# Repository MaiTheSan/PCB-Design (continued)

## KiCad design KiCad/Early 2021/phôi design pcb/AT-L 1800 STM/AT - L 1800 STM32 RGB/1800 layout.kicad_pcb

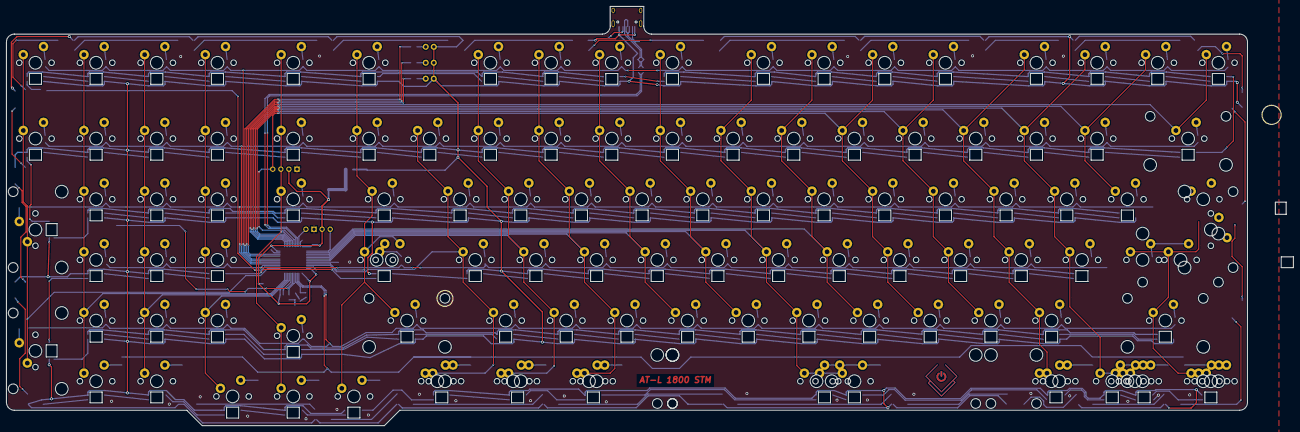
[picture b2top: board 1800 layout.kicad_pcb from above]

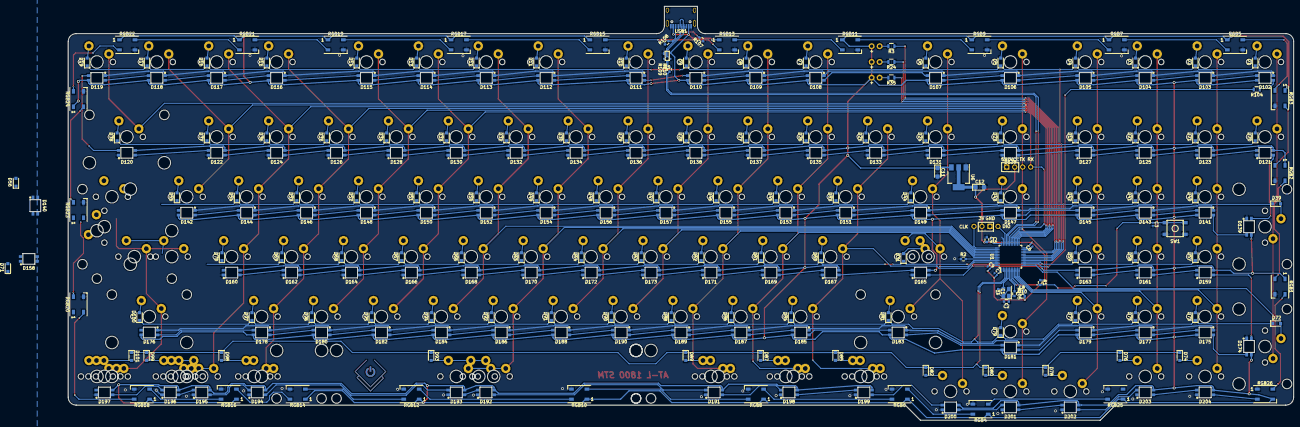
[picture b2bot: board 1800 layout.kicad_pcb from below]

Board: 2 copper layers, 404.1 x 131.6 mm, 380 parts (259 on the bottom side), 278 nets.

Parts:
C1, C2: 22pF; C_0603
C3, C5, C6, C7, C9: 0.1uF; C_0402_1005Metric
C4: 10uF; C_0603
C8: 10nF; C_0402_1005Metric
C10: 1uF; C_0603
C11, C12: >=22uF; CP_EIA-3216-12_Kemet-S
D1, D2, D3, D4, D5, D6, D7, D8, D9, D10, D11, D12, D13, D14, D15, D16, D17, D19, D20, D21, D22, D23, D24, D25, D26, D27, D28, D29, D30, D32, D33, D34, D35, D36, D37, D38, D39, D40, D41, D42, D43, D44, D45, D46, D47, D48, D49, D50, D51, D52, D53, D54, D55, D56, D57, D58, D59, D60, D61, D62, D63, D64, D65, D66, D67, D68, D69, D70, D71, D72, D73, D74, D75, D76, D77, D78, D79, D80, D81, D82, D83, D84, D85, D86, D87, D88, D89, D90, D91, D92, D93, D94, D95, D96, D97, D98, D99, D100, D101: D; D_SOD-323_HandSoldering
D18, D31: SOD123; D_SOD-323_HandSoldering
D102, D103, D104, D105, D106, D107, D108, D109, D110, D111, D112, D113, D114, D115, D116, D117, D118, D119, D140, D141, D142, D143, D144, D145, D146, D147, D148, D149, D150, D151, D152, D153, D154, D155, D156, D157, D175, D176, D177, D178, D179, D180, D181, D182, D183, D184, D185, D186, D187, D188, D189, D190: SK6812; RGB-6028_FLIPPED
D120, D121, D122, D123, D124, D125, D126, D127, D128, D129, D130, D131, D132, D133, D134, D135, D136, D137, D138, D139, D158, D159, D160, D161, D162, D163, D164, D165, D166, D167, D168, D169, D170, D171, D172, D173, D174, D191, D192, D193, D194, D195, D196, D197, D198, D199, D200, D201, D202, D203, D204: SK6812; RGB-6028
LOGO1: Logo_Open_Hardware_Large; sanpjxlogo
Led1, Led2, Led3: LED; MXOnly-LEDONLY-MID
MX_1, MX_2, MX_3, MX_4, MX_5, MX_6, MX_7, MX_8, MX_9, MX_10: 1U; MXOnly-1U-NoLED
MX_'1: 1U; MXOnly-1U-NoLED
MX_+1: 1U; MXOnly-1U-NoLED
MX_-1: 1U; MXOnly-1U-NoLED
MX_/?/1: 1U; MXOnly-1U-NoLED
MX_;1: 1U; MXOnly-1U-NoLED
MX_<1: 1U; MXOnly-1U-NoLED
MX_>1: 1U; MXOnly-1U-NoLED
MX_A1: 1U; MXOnly-1U-NoLED
MX_ALT1: 1,5U; MXOnly-1.5U-NoLED
MX_ALT2: 1,25U FLIPPED; MXOnly-1.25U-NoLED
MX_BkSp1: 2U FLIPPED; MXOnly-2U-NoLED
MX_CapLk1: 1,75U; MXOnly-1.75U-NoLED
MX_CapLk2: 1,25U FLIPPED; MXOnly-1.25U-NoLED
MX_D1: 1U; MXOnly-1U-NoLED
MX_Delete1: 1U; MXOnly-1U-NoLED
MX_Down1: 1U; MXOnly-1U-NoLED
MX_E1: 1U; MXOnly-1U-NoLED
MX_ENTER1: 2x2.25U ISO enter; MXOnly-ISO-ROTATED-ReversedStabilizers-NoLED
MX_ENTER2: 2,25U FLIPPED; MXOnly-2.25U-ReversedStabilizers-NoLED
MX_ESC1: 1U FLIPPED; MXOnly-1U-NoLED
MX_F1, MX_F4, MX_F5, MX_F6, MX_F8, MX_F10, MX_F11: 1U; MXOnly-1U-NoLED
MX_F2, MX_F3, MX_F7, MX_F9, MX_F12, MX_F13: 1U FLIPPED; MXOnly-1U-NoLED
MX_FN1, MX_FN2, MX_FN3, MX_FN41: 1U; MXOnly-1U-NoLED
MX_FN4: 1U_FLIPPED; MXOnly-1U-NoLED
MX_G1: 1U; MXOnly-1U-NoLED
MX_H1: 1U; MXOnly-1U-NoLED
MX_I1: 1U; MXOnly-1U-NoLED
MX_J1: 1U; MXOnly-1U-NoLED
MX_K1: 1U; MXOnly-1U-NoLED
MX_L1: 1U; MXOnly-1U-NoLED
MX_LControl1: 1,5U; MXOnly-1.5U-NoLED
MX_LControl2: 1,25U FLIPPED; MXOnly-1.25U-NoLED
MX_LShift1: 2,25U; MXOnly-2.25U-NoLED
MX_LWin1: 1U; MXOnly-1U-NoLED
MX_LWin2: 1,25U NoLed; MXOnly-1.25U-NoLED
MX_Left1: 1U; MXOnly-1U-NoLED
MX_O1: 1U; MXOnly-1U-NoLED
MX_P1: 1U; MXOnly-1U-NoLED
MX_Q1: 1U; MXOnly-1U-NoLED
MX_R1: 1U; MXOnly-1U-NoLED
MX_RAlt1: 1,25U; MXOnly-1.25U-NoLED
MX_RAlt2: 1,5U FLIPPED; MXOnly-1.5U-NoLED
MX_RAlt3: 1,5U; MXOnly-1.5U-NoLED
MX_RControl1: 1,25U NoLed; MXOnly-1.25U-NoLED
MX_RControl2: 1U FLIPPED; MXOnly-1U-NoLED
MX_RControl3: 1,5U FLIPPED; MXOnly-1.5U-NoLED
MX_RShift1: 2,75U FLIPPED; MXOnly-2.75U-NoLED
MX_RWin1: NoLed; MXOnly-1.25U-NoLED
MX_RWin2: 1,5U; MXOnly-1.5U-NoLED
MX_RWin3: 1U; MXOnly-1U-NoLED
MX_S1: 1U; MXOnly-1U-NoLED
MX_SpaceBar1, MX_SpaceBar2: 6,25U FLIPPED; MXOnly-6.25U-ReversedStabilizers-NoLED
MX_SpaceBar3: 7U; MXOnly-7U-ReversedStabilizers-NoLED
MX_T1: 1U; MXOnly-1U-NoLED
MX_U1: 1U; MXOnly-1U-NoLED
MX_W1: 1U; MXOnly-1U-NoLED
MX_Y1: 1U; MXOnly-1U-NoLED
MX_[1: 1U; MXOnly-1U-NoLED
MX_]1: 1U; MXOnly-1U-NoLED
MX_`~1: 1U; MXOnly-1U-NoLED
MX_b1: 1U; MXOnly-1U-NoLED
MX_c1: 1U; MXOnly-1U-NoLED
MX_insert1: 1U; MXOnly-1U-NoLED
MX_m1: 1U; MXOnly-1U-NoLED
MX_n1: 1U; MXOnly-1U-NoLED
MX_num1, MX_num2, MX_num3, MX_num4, MX_num5, MX_num6, MX_num7, MX_num8, MX_num9, MX_num10: 1U; MXOnly-1U-NoLED
MX_num*1: 1U; MXOnly-1U-NoLED
MX_num+1: 2U FLIPPED; MXOnly-2U-NoLED
MX_num-1: 1U; MXOnly-1U-NoLED
MX_num/1: 1U; MXOnly-1U-NoLED
MX_numDel1: 1U; MXOnly-1U-NoLED
MX_numEnter1: 2U; MXOnly-2U-NoLED
MX_numLk1: 1U; MXOnly-1U-NoLED
MX_right1: 1U; MXOnly-1U-NoLED
MX_tab1: 1,5U; MXOnly-1.5U-NoLED
MX_up1: 1U; MXOnly-1U-NoLED
MX_v1: 1U; MXOnly-1U-NoLED
MX_x1: 1U; MXOnly-1U-NoLED
MX_z1: 1U; MXOnly-1U-NoLED
MX_|\1: 1U; MXOnly-1U-NoLED
MX_|\2: 1.5U FLIPPED; MXOnly-1.5U-NoLED
R1, R2: 10k; C_0603
R3, R24, R35: 300; R_0805
R104: 500; R_0805
R105: 390; C_0603
R107, R108: 5.1k; C_0603
R109, R110: 22; C_0603
RGB1, RGB2, RGB3, RGB4, RGB5, RGB6, RGB7, RGB8, RGB9, RGB10, RGB11, RGB12, RGB13, RGB14, RGB15, RGB16, RGB17, RGB18, RGB19, RGB20, RGB21, RGB22, RGB23, RGB24, RGB25, RGB26: WS2812B; LED_WS2812B_PLCC4_5.0x5.0mm_P3.2mm
SW1: SW_Push; SKQG-1155865
U1: STM32F303CCTx; LQFP-48_7x7mm_P0.5mm
U2, U3: OLED-Pin; 0.91_SSD1306_OLED
U5: PRTR5V0U2X; SOT143B
U6: AMS1117-3.3; SOT-223-3_TabPin2
USB1: HRO-TYPE-C-31-M-12; HRO-TYPE-C-31-M-12-Assembly
Y1: 16Mhz; Crystal_SMD_3225-4Pin_3.2x2.5mm

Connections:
+5V: C11.1, D102.1, D103.1, D104.1, D105.1, D106.1, D107.1, D108.1, D109.1, D110.1, D111.1, D112.1, D113.1, D114.1, D115.1, D116.1, D117.1, D118.1, D119.1, D120.1, D121.1, D122.1, D123.1, D124.1, D125.1, D126.1, D127.1, D128.1, D129.1, D130.1, D131.1, D132.1, D133.1, D134.1, D135.1, D136.1, D137.1, D138.1, D139.1, D140.1, D141.1, D142.1, D143.1, D144.1, D145.1, D146.1, D147.1, D148.1, D149.1, D150.1, D151.1, D152.1, D153.1, D154.1, D155.1, D156.1, D157.1, D158.1, D159.1, D160.1, D161.1, D162.1, D163.1, D164.1, D165.1, D166.1, D167.1, D168.1, D169.1, D170.1, D171.1, D172.1, D173.1, D174.1, D175.1, D176.1, D177.1, D178.1, D179.1, D180.1, D181.1, D182.1, D183.1, D184.1, D185.1, D186.1, D187.1, D188.1, D189.1, D190.1, D191.1, D192.1, D193.1, D194.1, D195.1, D196.1, D197.1, D198.1, D199.1, D200.1, D201.1, D202.1, D203.1, D204.1, Led1.2, Led2.2, Led3.2, RGB1.1, RGB2.1, RGB3.1, RGB4.1, RGB5.1, RGB6.1, RGB7.1, RGB8.1, RGB9.1, RGB10.1, RGB11.1, RGB12.1, RGB13.1, RGB14.1, RGB15.1, RGB16.1, RGB17.1, RGB18.1, RGB19.1, RGB20.1, RGB21.1, RGB22.1, RGB23.1, RGB24.1, RGB25.1, RGB26.3, U5.4, U6.3, USB1.2, USB1.11
/R+: R110.2, U5.3, USB1.5, USB1.7
/R-: R109.2, U5.2, USB1.6, USB1.8
CapsLed: R3.1, U1.19
Col0: MX_FN1.1, MX_num+1.1, MX_num-1.1, MX_numEnter1.1, U1.13
Col1: MX_FN2.1, MX_num1.1, MX_num2.1, MX_num3.1, MX_num4.1, MX_num*1.1, U1.12
Col2: MX_FN3.1, MX_num5.1, MX_num6.1, MX_num7.1, MX_num/1.1, MX_numDel1.1, U1.11
Col3: MX_FN4.1, MX_Left1.1, MX_num8.1, MX_num9.1, MX_num10.1, MX_numLk1.1, U1.10
Col4: MX_Delete1.1, MX_Down1.1, MX_FN41.1, MX_insert1.1, MX_up1.1, U1.30, U3.3
Col5: MX_CapLk1.2, MX_CapLk2.1, MX_ESC1.1, MX_LShift1.1, MX_`~1.1, MX_right1.1, MX_tab1.1, U1.45
Col6: MX_1.1, MX_A1.1, MX_LControl1.1, MX_LControl2.1, MX_Q1.1, MX_z1.1, U1.46
Col7: MX_2.1, MX_F1.1, MX_LWin1.1, MX_LWin2.1, MX_S1.1, MX_W1.1, MX_x1.1, U1.43
Col8: MX_3.1, MX_ALT1.1, MX_ALT2.1, MX_D1.1, MX_E1.1, MX_F2.1, MX_c1.1, U1.42
Col9: MX_4.1, MX_F3.1, MX_F4.1, MX_R1.1, MX_v1.1, U1.41
Col10: MX_5.1, MX_F5.1, MX_G1.1, MX_T1.1, MX_b1.1, U1.40
Col11: MX_6.1, MX_F6.1, MX_H1.1, MX_SpaceBar1.1, MX_SpaceBar2.1, MX_SpaceBar3.1, MX_Y1.1, MX_n1.1, U1.39
Col12: MX_7.1, MX_F7.1, MX_J1.1, MX_U1.1, MX_m1.1, U1.38
Col13: MX_8.1, MX_<1.1, MX_F8.1, MX_I1.1, MX_K1.1, U1.31, U3.4
Col14: MX_9.1, MX_>1.1, MX_F9.1, MX_L1.1, MX_O1.1, U1.29
Col15: MX_10.1, MX_/?/1.1, MX_;1.1, MX_F10.1, MX_P1.1, MX_RAlt1.1, MX_RAlt2.1, U1.28
Col16: MX_'1.1, MX_-1.1, MX_F11.1, MX_RAlt3.1, MX_RWin1.1, MX_RWin2.1, MX_RWin3.1, MX_[1.1, U1.27
Col17: MX_+1.1, MX_F12.1, MX_]1.1, U1.26
Col18: MX_BkSp1.1, MX_ENTER1.1, MX_ENTER2.1, MX_F13.1, MX_RControl1.1, MX_RControl2.1, MX_RControl3.1, MX_RShift1.1, MX_|\1.1, MX_|\2.1, U1.25
D+: R109.1, U1.33
D-: R110.1, U1.32
GND: C1.2, C2.2, C3.2, C4.1, C5.1, C6.1, C7.1, C8.1, C9.1, C10.1, C11.2, C12.2, D102.3, D103.3, D104.3, D105.3, D106.3, D107.3, D108.3, D109.3, D110.3, D111.3, D112.3, D113.3, D114.3, D115.3, D116.3, D117.3, D118.3, D119.3, D120.3, D121.3, D122.3, D123.3, D124.3, D125.3, D126.3, D127.3, D128.3, D129.3, D130.3, D131.3, D132.3, D133.3, D134.3, D135.3, D136.3, D137.3, D138.3, D139.3, D140.3, D141.3, D142.3, D143.3, D144.3, D145.3, D146.3, D147.3, D148.3, D149.3, D150.3, D151.3, D152.3, D153.3, D154.3, D155.3, D156.3, D157.3, D158.3, D159.3, D160.3, D161.3, D162.3, D163.3, D164.3, D165.3, D166.3, D167.3, D168.3, D169.3, D170.3, D171.3, D172.3, D173.3, D174.3, D175.3, D176.3, D177.3, D178.3, D179.3, D180.3, D181.3, D182.3, D183.3, D184.3, D185.3, D186.3, D187.3, D188.3, D189.3, D190.3, D191.3, D192.3, D193.3, D194.3, D195.3, D196.3, D197.3, D198.3, D199.3, D200.3, D201.3, D202.3, D203.3, D204.3, R2.1, R107.1, R108.1, RGB1.3, RGB2.3, RGB3.3, RGB4.3, RGB5.3, RGB6.3, RGB7.3, RGB8.3, RGB9.3, RGB10.3, RGB11.3, RGB12.3, RGB13.3, RGB14.3, RGB15.3, RGB16.3, RGB17.3, RGB18.3, RGB19.3, RGB20.3, RGB21.3, RGB22.3, RGB23.3, RGB24.3, RGB25.3, RGB26.1, SW1.1, U1.8, U1.23, U1.35, U1.47, U2.1, U3.1, U5.1, U6.1, USB1.1, USB1.12, USB1.13, Y1.2, Y1.4
LedRGB: D102.4, R104.1
LedRGBStrip: D204.2, RGB26.2
unnamed: C1.1, U1.5, Y1.3
unnamed: C2.1, R105.2, Y1.1
unnamed: C3.1, R1.2, SW1.2, U1.7
unnamed: D1.2, MX_FN1.2
unnamed: D2.2, MX_FN2.2
unnamed: D3.2, MX_FN3.2
unnamed: D4.2, MX_FN4.2
unnamed: D5.2, MX_FN41.2
unnamed: D6.2, MX_ESC1.2
unnamed: D7.2, MX_F1.2
unnamed: D8.2, MX_F2.2
unnamed: D9.2, MX_F3.2
unnamed: D10.2, MX_F5.2
unnamed: D11.2, MX_F6.2
unnamed: D12.2, MX_F7.2
unnamed: D13.2, MX_F8.2
unnamed: D14.2, MX_F9.2
unnamed: D15.2, MX_F10.2
unnamed: D16.2, MX_F11.2
unnamed: D17.2, MX_F12.2
unnamed: D18.2, MX_numLk1.2
unnamed: D19.2, MX_F13.2
unnamed: D20.2, MX_num-1.2
unnamed: D21.2, MX_num*1.2
unnamed: D22.2, MX_num/1.2
unnamed: D23.2, MX_insert1.2
unnamed: D24.2, MX_`~1.2
unnamed: D25.2, MX_1.2
unnamed: D26.2, MX_2.2
unnamed: D27.2, MX_3.2
unnamed: D28.2, MX_4.2
unnamed: D29.2, MX_5.2
unnamed: D30.2, MX_6.2
unnamed: D31.2, MX_CapLk1.1, MX_CapLk2.2
unnamed: D32.2, MX_7.2
unnamed: D33.2, MX_8.2
unnamed: D34.2, MX_9.2
unnamed: D35.2, MX_10.2
unnamed: D36.2, MX_-1.2
unnamed: D37.2, MX_+1.2
unnamed: D38.2, MX_BkSp1.2
unnamed: D39.2, MX_num+1.2
unnamed: D40.2, MX_num1.2
unnamed: D41.2, MX_num5.2
unnamed: D42.2, MX_num8.2
unnamed: D43.2, MX_Delete1.2
unnamed: D44.2, MX_tab1.2
unnamed: D45.2, MX_W1.2
unnamed: D46.2, MX_E1.2
unnamed: D47.2, MX_R1.2
unnamed: D48.2, MX_T1.2
unnamed: D49.2, MX_Y1.2
unnamed: D50.2, MX_U1.2
unnamed: D51.2, MX_I1.2
unnamed: D52.2, MX_O1.2
unnamed: D53.2, MX_P1.2
unnamed: D54.2, MX_[1.2
unnamed: D55.2, MX_]1.2
unnamed: D56.2, MX_|\1.2, MX_|\2.2
unnamed: D57.2, MX_num2.2
unnamed: D58.2, MX_num6.2
unnamed: D59.2, MX_num9.2
unnamed: D60.2, MX_A1.2
unnamed: D61.2, MX_S1.2
unnamed: D62.2, MX_D1.2
unnamed: D63.2, MX_F4.2
unnamed: D64.2, MX_G1.2
unnamed: D65.2, MX_H1.2
unnamed: D66.2, MX_J1.2
unnamed: D67.2, MX_K1.2
unnamed: D68.2, MX_L1.2
unnamed: D69.2, MX_;1.2
unnamed: D70.2, MX_'1.2
unnamed: D71.2, MX_ENTER1.2, MX_ENTER2.2
unnamed: D72.2, MX_numEnter1.2
unnamed: D73.2, MX_num3.2
unnamed: D74.2, MX_num4.2
unnamed: D75.2, MX_num7.2
unnamed: D76.2, MX_numDel1.2
unnamed: D77.2, MX_num10.2
unnamed: D78.2, MX_Left1.2
unnamed: D79.2, MX_up1.2
unnamed: D80.2, MX_Down1.2
unnamed: D81.2, MX_LShift1.2
unnamed: D82.2, MX_right1.2
unnamed: D83.2, MX_Q1.2
unnamed: D84.2, MX_z1.2
unnamed: D85.2, MX_LControl1.2, MX_LControl2.2
unnamed: D86.2, MX_x1.2
unnamed: D87.2, MX_LWin1.2, MX_LWin2.2
unnamed: D88.2, MX_c1.2
unnamed: D89.2, MX_ALT1.2, MX_ALT2.2
unnamed: D90.2, MX_v1.2
unnamed: D91.2, MX_b1.2
unnamed: D92.2, MX_n1.2
unnamed: D93.2, MX_SpaceBar1.2, MX_SpaceBar2.2, MX_SpaceBar3.2
unnamed: D94.2, MX_m1.2
unnamed: D95.2, MX_<1.2
unnamed: D96.2, MX_>1.2
unnamed: D97.2, MX_/?/1.2
unnamed: D98.2, MX_RAlt1.2, MX_RAlt2.2
unnamed: D99.2, MX_RAlt3.2, MX_RWin1.2, MX_RWin2.2, MX_RWin3.2
unnamed: D100.2, MX_RShift1.2
unnamed: D101.2, MX_RControl1.2, MX_RControl2.2, MX_RControl3.2
unnamed: D102.2, D103.4
unnamed: D103.2, D104.4
unnamed: D104.2, D105.4
unnamed: D105.2, D106.4
unnamed: D106.2, D107.4
unnamed: D107.2, D108.4
unnamed: D108.2, D109.4
unnamed: D109.2, D110.4
unnamed: D110.2, D111.4
unnamed: D111.2, D112.4
unnamed: D112.2, D113.4
unnamed: D113.2, D114.4
unnamed: D114.2, D115.4
unnamed: D115.2, D116.4
unnamed: D116.2, D117.4
unnamed: D117.2, D118.4
unnamed: D118.2, D119.4
unnamed: D120.2, D122.4
unnamed: D121.4, D123.2
unnamed: D122.2, D124.4
unnamed: D123.4, D125.2
unnamed: D124.2, D126.4
unnamed: D125.4, D127.2
unnamed: D126.2, D128.4
unnamed: D127.4, D129.2
unnamed: D128.2, D130.4
unnamed: D129.4, D131.2
unnamed: D130.2, D132.4
unnamed: D131.4, D133.2
unnamed: D132.2, D134.4
unnamed: D133.4, D135.2
unnamed: D134.2, D136.4
unnamed: D135.4, D137.2
unnamed: D136.2, D138.4
unnamed: D137.4, D138.2
unnamed: D139.2, D141.4
unnamed: D140.4, D142.2
unnamed: D141.2, D143.4
unnamed: D142.4, D144.2
unnamed: D143.2, D145.4
unnamed: D144.4, D146.2
unnamed: D145.2, D147.4
unnamed: D146.4, D148.2
unnamed: D147.2, D149.4
unnamed: D148.4, D150.2
unnamed: D149.2, D151.4
unnamed: D150.4, D152.2
unnamed: D151.2, D153.4
unnamed: D152.4, D154.2
unnamed: D153.2, D155.4
unnamed: D154.4, D156.2
unnamed: D155.2, D157.4
unnamed: D156.4, D157.2
unnamed: D158.2, D160.4
unnamed: D159.2, D174.4
unnamed: D159.4, D161.2
unnamed: D160.2, D162.4
unnamed: D161.4, D163.2
unnamed: D162.2, D164.4
unnamed: D163.4, D165.2
unnamed: D164.2, D166.4
unnamed: D165.4, D167.2
unnamed: D166.2, D168.4
unnamed: D167.4, D169.2
unnamed: D168.2, D170.4
unnamed: D169.4, D171.2
unnamed: D170.2, D172.4
unnamed: D171.4, D173.2
unnamed: D172.2, D173.4
unnamed: D175.2, D177.4
unnamed: D176.4, D178.2
unnamed: D177.2, D179.4
unnamed: D178.4, D180.2
unnamed: D179.2, D181.4
unnamed: D180.4, D182.2
unnamed: D181.2, D183.4
unnamed: D182.4, D184.2
unnamed: D183.2, D185.4
unnamed: D184.4, D186.2
unnamed: D185.2, D187.4
unnamed: D186.4, D188.2
unnamed: D187.2, D189.4
unnamed: D188.4, D190.2
unnamed: D189.2, D190.4
unnamed: D191.2, D198.4
unnamed: D191.4, D192.2
unnamed: D192.4, D193.2
unnamed: D193.4, D194.2
unnamed: D194.4, D195.2
unnamed: D195.4, D196.2
unnamed: D196.4, D197.2
unnamed: D198.2, D199.4
unnamed: D199.2, D200.4
unnamed: D200.2, D201.4
unnamed: D201.2, D202.4
unnamed: D202.2, D203.4
unnamed: D203.2, D204.4
unnamed: Led1.1, R3.2
unnamed: Led2.1, R24.2
unnamed: Led3.1, R35.2
unnamed: R2.2, U1.44
unnamed: R104.2, U1.14
unnamed: R105.1, U1.6
unnamed: R107.2, USB1.4
unnamed: R108.2, USB1.10
unnamed: RGB1.2, RGB2.4
unnamed: RGB1.4, RGB26.4
unnamed: RGB2.2, RGB3.4
unnamed: RGB3.2, RGB5.4
unnamed: RGB4.4, RGB6.2
unnamed: RGB5.2, RGB7.4
unnamed: RGB6.4, RGB8.2
unnamed: RGB7.2, RGB9.4
unnamed: RGB8.4, RGB10.2
unnamed: RGB10.4, RGB12.2
unnamed: RGB11.2, RGB13.4
unnamed: RGB9.2, RGB11.4
unnamed: RGB12.4, RGB14.2
unnamed: RGB13.2, RGB15.4
unnamed: RGB14.4, RGB16.2
unnamed: RGB15.2, RGB17.4
unnamed: RGB16.4, RGB18.2
unnamed: RGB17.2, RGB19.4
unnamed: RGB18.4, RGB20.2
unnamed: RGB19.2, RGB21.4
unnamed: RGB20.4, RGB23.2
unnamed: RGB21.2, RGB22.4
unnamed: RGB22.2, RGB24.4
unnamed: RGB23.4, RGB24.2
unnamed: RGB4.2, RGB25.4
NumLed: R35.1, U1.22
Row0: D1.1, D2.1, D3.1, D4.1, D5.1, D6.1, D7.1, D8.1, D9.1, D10.1, D11.1, D12.1, D13.1, D14.1, D15.1, D16.1, D17.1, D19.1, U1.18
Row1: D18.1, D20.1, D21.1, D22.1, D23.1, D24.1, D25.1, D26.1, D27.1, D28.1, D29.1, D30.1, D32.1, D33.1, D34.1, D35.1, D36.1, D37.1, D38.1, U1.17
Row2: D39.1, D40.1, D41.1, D42.1, D43.1, D44.1, D45.1, D46.1, D47.1, D48.1, D49.1, D50.1, D51.1, D52.1, D53.1, D54.1, D55.1, D56.1, D83.1, U1.16
Row3: D31.1, D57.1, D58.1, D59.1, D60.1, D61.1, D62.1, D63.1, D64.1, D65.1, D66.1, D67.1, D68.1, D69.1, D70.1, D71.1, U1.15
Row4: D72.1, D73.1, D75.1, D77.1, D79.1, D81.1, D84.1, D86.1, D88.1, D90.1, D91.1, D92.1, D94.1, D95.1, D96.1, D97.1, D100.1, U1.3
Row5: D74.1, D76.1, D78.1, D80.1, D82.1, D85.1, D87.1, D89.1, D93.1, D98.1, D99.1, D101.1, U1.4
SWCLK: U1.37, U2.3
SWDIO: U1.34, U2.4
ScrollLed: R24.1, U1.21
VCC: C4.2, C5.2, C6.2, C7.2, C8.2, C9.2, C10.2, C12.1, R1.1, U1.1, U1.9, U1.24, U1.36, U1.48, U2.2, U3.2, U6.2
out1: D119.2, D120.4
out2: D121.2, D139.4
out3: D140.2, D158.4
out4: D174.2, D175.4
out5: D176.2, D197.4

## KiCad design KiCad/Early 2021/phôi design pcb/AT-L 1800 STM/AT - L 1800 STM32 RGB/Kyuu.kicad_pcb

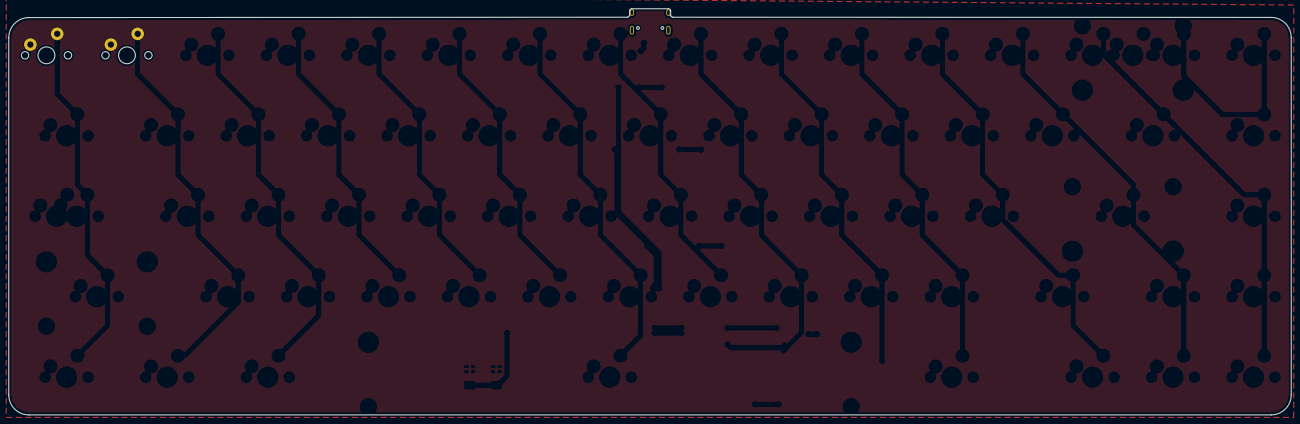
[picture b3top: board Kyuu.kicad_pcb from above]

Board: 2 copper layers, 303.6 x 96.1 mm, 3 parts (1 on the bottom side), 2 nets.

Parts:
MX1, MX2: MX-NoLED; MXOnly-1U-NoLED
USB1: HRO-TYPE-C-31-M-12; HRO-TYPE-C-31-M-12-Assembly

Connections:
/D+: USB1.6, USB1.8
/D-: USB1.5, USB1.7

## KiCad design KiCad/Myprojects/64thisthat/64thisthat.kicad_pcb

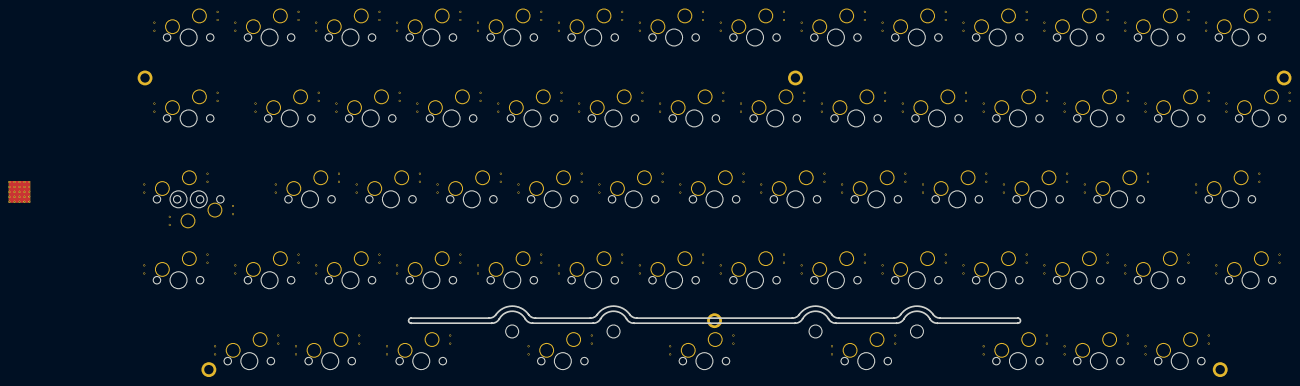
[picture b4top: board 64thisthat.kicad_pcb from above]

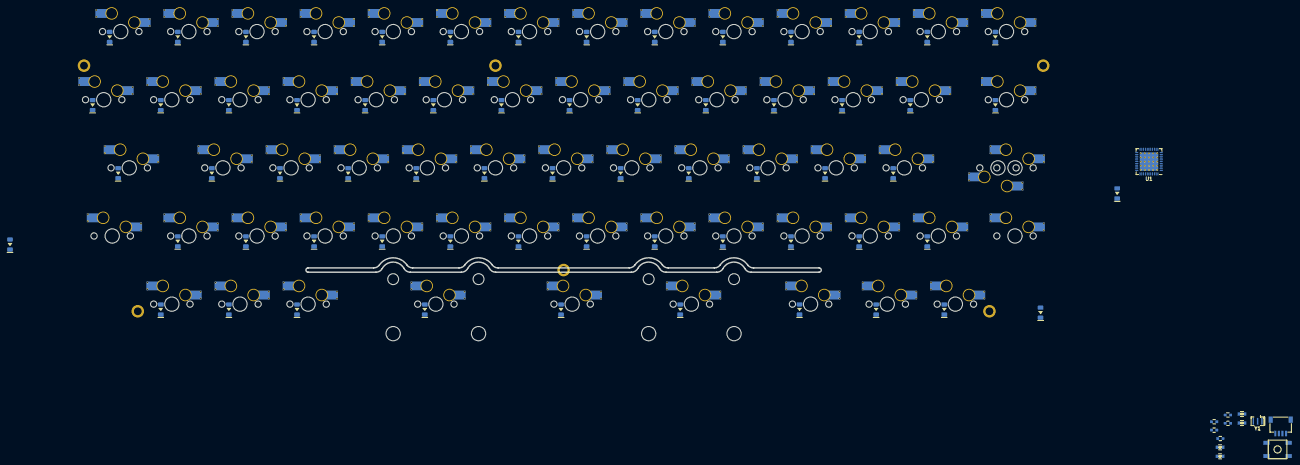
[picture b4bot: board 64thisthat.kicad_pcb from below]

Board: 2 copper layers, 148 parts (77 on the bottom side), 89 nets, no tracks yet.

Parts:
C1: 1uF; C_0603
C2: 10uF; C_0603
C3, C4, C5: 0.1uF; C_0603
D1, D2, D3, D4, D5, D6, D7, D8, D9, D10, D11, D12, D13, D14, D15, D16, D17, D18, D19, D20, D21, D22, D23, D24, D25, D26, D27, D28, D29, D30, D31, D32, D33, D34, D35, D36, D37, D38, D39, D40, D42, D43, D44, D45, D46, D47, D48, D49, D50, D51, D52, D53, D54, D55, D56, D60, D61, D62, D63, D64, D65, D66, D67, D68: 1N4148W; DIODE_1206_SawnsProjects
H4, H4#2, H4#3, H4#4, H4#5, H4#6: MountingHole; MountingHole_2.2mm_M2_ISO7380_Pad
J1: Daughterboard; JST-SR-4
MX1, MX2, MX3, MX4, MX5, MX6, MX7, MX8, MX9, MX10, MX11, MX12, MX13, MX14, MX16, MX17, MX18, MX19, MX20, MX21, MX22, MX23, MX24, MX25, MX26, MX27, MX28, MX30, MX31, MX32, MX33, MX34, MX35, MX36, MX37, MX38, MX39, MX40, MX44, MX45, MX46, MX47, MX48, MX49, MX50, MX51, MX52, MX53, MX54, MX55, MX60, MX61, MX66, MX67, MX68: 1U; MXOnly-1U-Hotswap-Sawns
MX15: 1.5U; MXOnly-1.5U-Hotswap-Sawns
MX29, MX42: 1.75U; MXOnly-1.75U-Hotswap-Sawns
MX41, MX43, MX56, MX57, MX64: 1.25U; MXOnly-1.25U-Hotswap-Sawns
MX63: 2.25U; MXOnly-2.25U-Hotswap-Sawns
MX65: 2.75U; MXOnly-2.75U-Hotswap-Sawns
R1, R4: 10k; R_0603
R2, R3: 22R; R_0603
SW1: SW_Push; SKQG-1155865-fix
U1: ATmega32U4-MU; QFN-44-1EP_7x7mm_P0.5mm_EP5.15x5.15mm_ThermalVias
Y1: 16MHz; Resonator_SMD_muRata_CSTxExxV-3Pin_3.0x1.1mm

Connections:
+5V: C2.2, C3.2, C4.2, C5.2, J1.1, R4.1, U1.2, U1.7, U1.14, U1.24, U1.34, U1.44
/M+: R2.1, U1.4
/M-: R3.2, U1.3
D+: J1.3, R2.2
D-: J1.2, R3.1
GND: C1.2, C2.1, C3.1, C4.1, C5.1, J1.4, R1.1, SW1.1, U1.5, U1.15, U1.23, U1.35, U1.43, U1.45, Y1.2
unnamed: C1.1, U1.6
unnamed: D1.2, MX15.2
unnamed: D2.2, MX16.2
unnamed: D3.2, MX17.2
unnamed: D4.2, MX18.2
unnamed: D5.2, MX19.2
unnamed: D6.2, MX20.2
unnamed: D7.2, MX1.2
unnamed: D8.2, MX2.2
unnamed: D9.2, MX3.2
unnamed: D10.2, MX4.2
unnamed: D11.2, MX5.2
unnamed: D12.2, MX6.2
unnamed: D13.2, MX7.2
unnamed: D14.2, MX8.2
unnamed: D15.2, MX9.2
unnamed: D16.2, MX10.2
unnamed: D17.2, MX11.2
unnamed: D18.2, MX12.2
unnamed: D19.2, MX13.2
unnamed: D20.2, MX14.2
unnamed: D21.2, MX21.2
unnamed: D22.2, MX22.2
unnamed: D23.2, MX23.2
unnamed: D24.2, MX24.2
unnamed: D25.2, MX25.2
unnamed: D26.2, MX26.2
unnamed: D27.2, MX27.2
unnamed: D28.2, MX28.2
unnamed: D29.2, MX29.2
unnamed: D30.2, MX30.2
unnamed: D31.2, MX31.2
unnamed: D32.2, MX32.2
unnamed: D33.2, MX33.2
unnamed: D34.2, MX34.2
unnamed: D35.2, MX35.2
unnamed: D36.2, MX36.2
unnamed: D37.2, MX37.2
unnamed: D38.2, MX38.2
unnamed: D39.2, MX39.2
unnamed: D40.2, MX40.2
unnamed: D42.2, MX42.2
unnamed: D43.2, MX43.2
unnamed: D44.2, MX44.2
unnamed: D45.2, MX45.2
unnamed: D46.2, MX46.2
unnamed: D47.2, MX47.2
unnamed: D48.2, MX48.2
unnamed: D49.2, MX49.2
unnamed: D50.2, MX50.2
unnamed: D51.2, MX51.2
unnamed: D52.2, MX52.2
unnamed: D53.2, MX53.2
unnamed: D54.2, MX54.2
unnamed: D55.2, MX55.2
unnamed: D56.2, MX56.2
unnamed: D60.2, MX60.2
unnamed: D61.2, MX61.2
unnamed: D62.2, MX57.2
unnamed: D63.2, MX63.2
unnamed: D64.2, MX64.2
unnamed: D65.2, MX65.2
unnamed: D66.2, MX66.2
unnamed: D67.2, MX67.2
unnamed: D68.2, MX68.2
unnamed: MX1.1, MX15.1, MX29.1, MX43.1
unnamed: MX10.1, MX24.1, MX38.1, MX52.1
unnamed: MX11.1, MX25.1, MX39.1, MX53.1, MX66.1
unnamed: MX12.1, MX26.1, MX40.1, MX54.1, MX67.1
unnamed: MX13.1, MX27.1, MX55.1, MX68.1
unnamed: MX14.1, MX28.1, MX42.1, MX56.1
unnamed: MX2.1, MX16.1, MX30.1, MX44.1, MX60.1
unnamed: MX3.1, MX17.1, MX31.1, MX45.1, MX61.1
unnamed: MX4.1, MX18.1, MX32.1, MX46.1, MX57.1
unnamed: MX5.1, MX19.1, MX33.1, MX47.1
unnamed: MX6.1, MX20.1, MX34.1, MX48.1, MX63.1
unnamed: MX7.1, MX21.1, MX35.1, MX49.1, MX64.1
unnamed: MX8.1, MX22.1, MX36.1, MX50.1
unnamed: MX9.1, MX23.1, MX37.1, MX51.1, MX65.1
unnamed: R1.2, U1.33
unnamed: R4.2, SW1.2, U1.13
unnamed: U1.16, Y1.3
unnamed: U1.17, Y1.1

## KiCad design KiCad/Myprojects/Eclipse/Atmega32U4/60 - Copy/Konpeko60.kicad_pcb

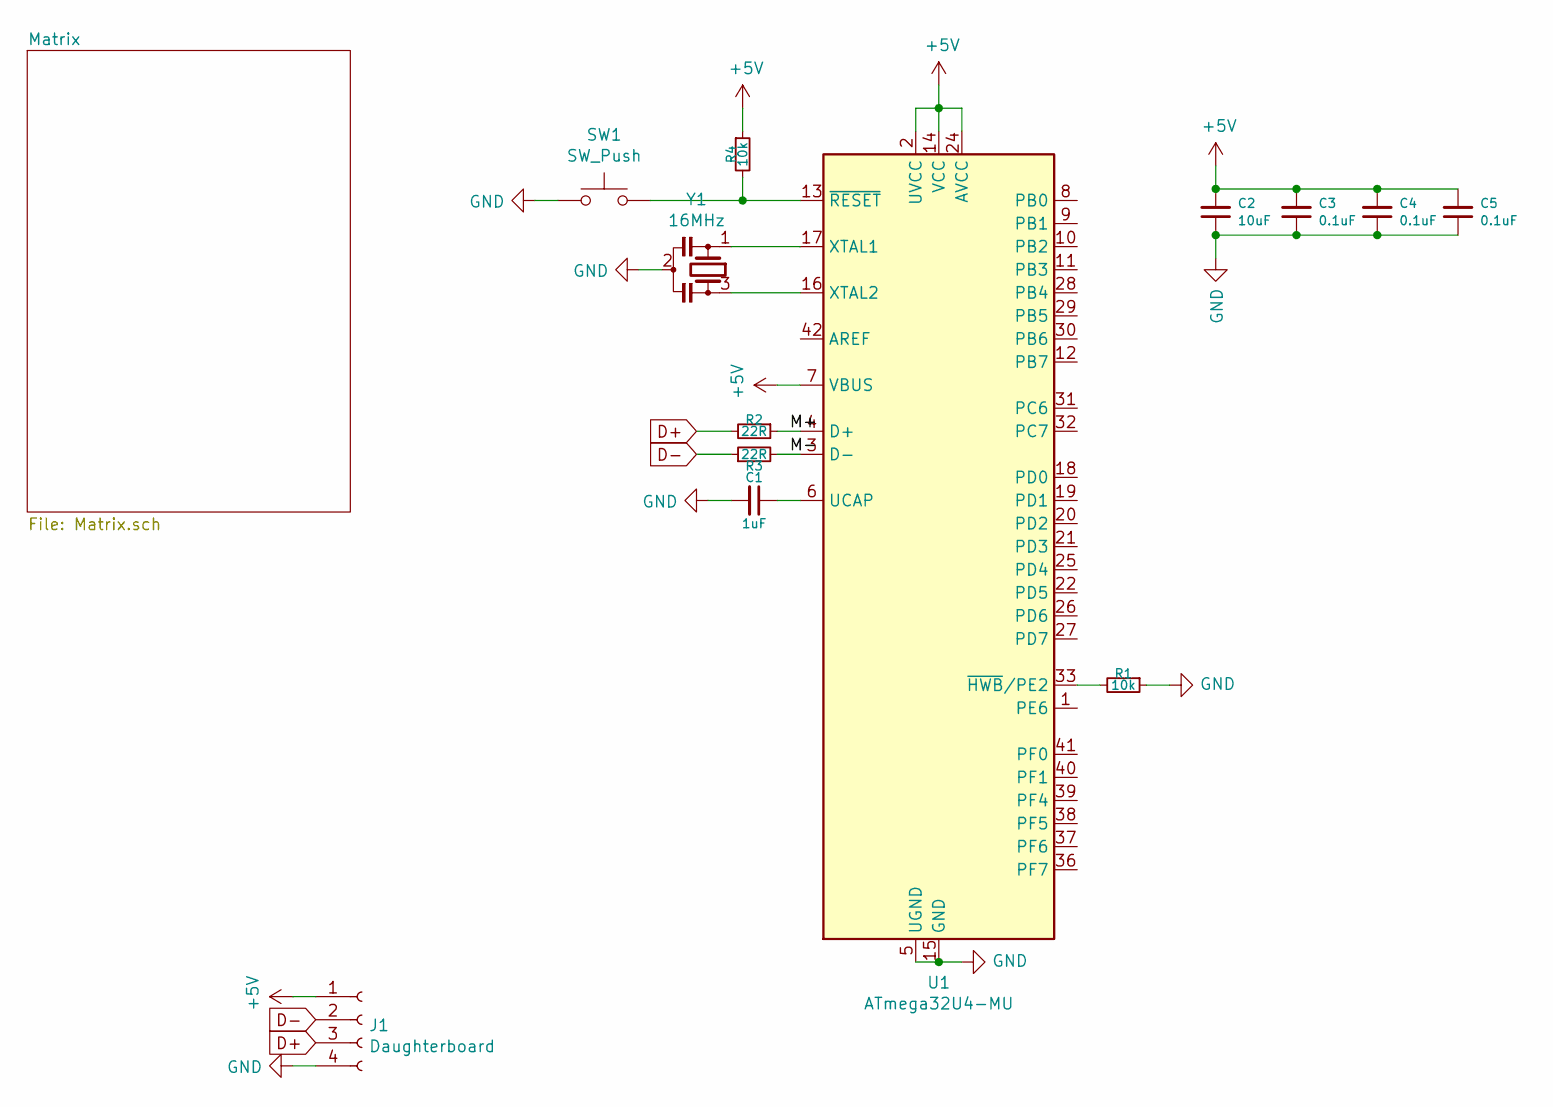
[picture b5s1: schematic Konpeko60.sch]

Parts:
C1: 1uF; C_0603
C2: 10uF; C_0603
C3, C4, C5: 0.1uF; C_0603
J1: Daughterboard; JST-SR-4
R1, R4: 10k; R_0603
R2, R3: 22R; R_0603
SW1: SW_Push; SKQG-1155865-fix
U1: ATmega32U4-MU; QFN-44-1EP_7x7mm_P0.5mm_EP5.15x5.15mm_ThermalVias
Y1: 16MHz; Resonator_SMD_muRata_CSTxExxV-3Pin_3.0x1.1mm

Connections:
+5V: C2.2, C3.2, C4.2, C5.2, J1.1, R4.1, U1.2 (UVCC), U1.7 (VBUS), U1.14 (VCC), U1.24 (AVCC), U1.34 (VCC), U1.44 (AVCC); also elsewhere on the board
/M+: R2.1, U1.4 (D+)
/M-: R3.2, U1.3 (D-)
D+: J1.3, R2.2
D-: J1.2, R3.1
GND: C1.2, C2.1, C3.1, C4.1, C5.1, J1.4, R1.1, SW1.1, U1.5 (UGND), U1.15 (GND), U1.23 (GND), U1.35 (GND), U1.43 (GND), U1.45 (GND), Y1.2; also elsewhere on the board
unnamed: C1.1, U1.6 (UCAP)
unnamed: R1.2, U1.33 (~HWB~/PE2)
unnamed: R4.2, SW1.2, U1.13 (~RESET)
unnamed: U1.16 (XTAL2), Y1.3
unnamed: U1.17 (XTAL1), Y1.1
